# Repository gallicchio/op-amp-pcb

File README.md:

# Discrete Transistor Op-Amp

The op-amp of *Learning the Art of Electronics* (Hayes and Horowitz, 2016), Lab 5L,
built from six 2N3904 / 2N3906 transistors on a 100 x 100 mm board whose silkscreen
*is* the schematic.  For a first electronics lab: every node has a loop to hang a
scope probe on, three DIP switches select the variants the book walks through, and
the inputs, output and power come in on BNCs and screw terminals.

> "I want you to build a relatively inexpensive educational Op-Amp PCB out of discrete
> transistors that I'll order from JLCPCB using only components that they have
> available and in stock ... The silkscreen should look exactly like the schematic ...
> The primary goal is clarity, simplicity, educational value, and ease of use for
> students in their first electronics lab class after having done most of chapter 4
> in Learning the Art of Electronics."

**Only prompts.** The whole project came from [a conversation with Claude](CLAUDE_CODE_CHAT.md):
the schematic, the board, the simulation, the fab files and these documents are all
written by the Python under `scripts/` and `sim/`, and nothing was drawn by hand.

## What it is

The book's three-stage op-amp, with the book's values:

* **Difference amplifier**, Q1 and Q2, 1.5 k collector load, gain about 11.
* **Tail**: Q6 as a current sink (62 k / 10 k / 1 k), or the plain 10 k resistor the
  book starts with, on switch **TAIL**.
* **Gain stage**: Q3, a PNP common-emitter stage, 330 ohm / 12 k, gain about 30, with
  the 100 pF Miller compensation capacitor on switch **COMPENSATION**.
* **Push-pull emitter follower**, Q4 and Q5, into the book's 10 k / 1 k divider whose
  tap **X** is the feedback point for a gain of 11.
* Switch **FEEDBACK** closes the loop as the x11 amplifier (X to IN-) or as a follower
  (OUT to IN-), or leaves it open so you wire your own feedback through the
  screw terminals.

What the board adds, so a class of first-year students can use it:

* An **OFFSET NULL** trimmer between the two emitters (50 ohm, wiper to the tail).
* A **1 k in series with the 100 pF**, which cancels the Miller zero and makes the
  follower stable; COMPENSATION 2 shorts it so the book's bare 100 pF can be heard ringing.
* **Input protection**: 1 k in series with each input and anti-parallel 1N4148s between
  the bases, so no base-emitter junction ever sees its 6 V reverse breakdown.
* **Output protection** in one part: R17, 330 ohm from the push-pull to OUT, inside
  the loop, so a shorted output draws about 46 mA and Q4 and Q5 stay cool.  It also
  keeps a cable on OUT from making the follower ring.
* **Reverse-supply protection** (a Schottky in each rail) and a green LED per rail.
* 18 probe loops, four of them ground (one per scope channel), placed on every node
  the book asks you to look at.  Dashed boxes name each stage on the silkscreen, and
  every transistor sits inside its own symbol with B, C and E marked.

Parts cost about $7.79 in parts per board at JLCPCB; the fixed assembly fees make the
first board about $70 and each further one about $9, so about $15 each for 10 assembled boards.  See
[docs/MANUFACTURING.md](docs/MANUFACTURING.md).

## Using it

[docs/HANDBOOK.md](docs/HANDBOOK.md) is the student and instructor guide: how to
power it, what every switch and loop does, the quiescent voltage at every loop, the
bring-up order for a new board, and a set of exercises that follow Lab 5L stage by
stage.  The back of the board carries the short version.

## Building the files

Needs KiCad 10 (an AppImage is enough), Python 3 with `Pillow`, `pdftoppm`
(poppler-utils) for the images and, optionally, `libngspice` for the simulation.

```bash
git clone https://github.com/gallicchio/op-amp-pcb.git
cd op-amp-pcb
export KICAD_APPIMAGE=$HOME/.local/bin/kicad-10.0.7-x86_64.AppImage   # or kicad-cli on PATH
./make.py              # footprints, models, simulation, schematic, board, checks, fab files, docs
./make.py --clean      # delete everything it generates
```

The build stops on any ERC or DRC violation, on any of the 110 circuit assertions
that read the exported netlist back against the book's circuit, on a schematic text
overlap, on a fab-package problem (an order code whose JLCPCB description no longer
matches, a QR code that does not decode from the board file) and on any number in
these documents that no longer matches the build.

## Layout

```
make.py                one command builds and checks everything
scripts/parts.py       every part: value, footprint, LCSC code, stock, JLCPCB rotation
scripts/layout.py      the board: placements, the silkscreen wires, texts and boxes
scripts/gen_sch.py     writes hardware/opamp.kicad_sch
scripts/gen_pcb.py     writes hardware/opamp.kicad_pcb (copper follows the silk wires)
scripts/check_*.py     the netlist, the schematic sheet and the fab package
sim/opamp_sim.py       ngspice: operating point, loop gain, step response, swing, null
out/opamp/             gerbers, BOM, CPL (native and JLCPCB), prints, PLACEMENT_CHECKS
docs/                  MANUFACTURING, HANDBOOK, DESIGN_NOTES, images
```

## More

* [docs/DESIGN_NOTES.md](docs/DESIGN_NOTES.md): every departure from the book and why,
  the simulation numbers, the risks for a first board and the rev B list.
* [CLAUDE_CODE_CHAT.md](CLAUDE_CODE_CHAT.md): the conversation that produced it.

Circuit: Hayes and Horowitz.  Board: Jason Gallicchio and Claude.  Hardware under
CERN-OHL-P-2.0, scripts under MIT; see [LICENSE](LICENSE).

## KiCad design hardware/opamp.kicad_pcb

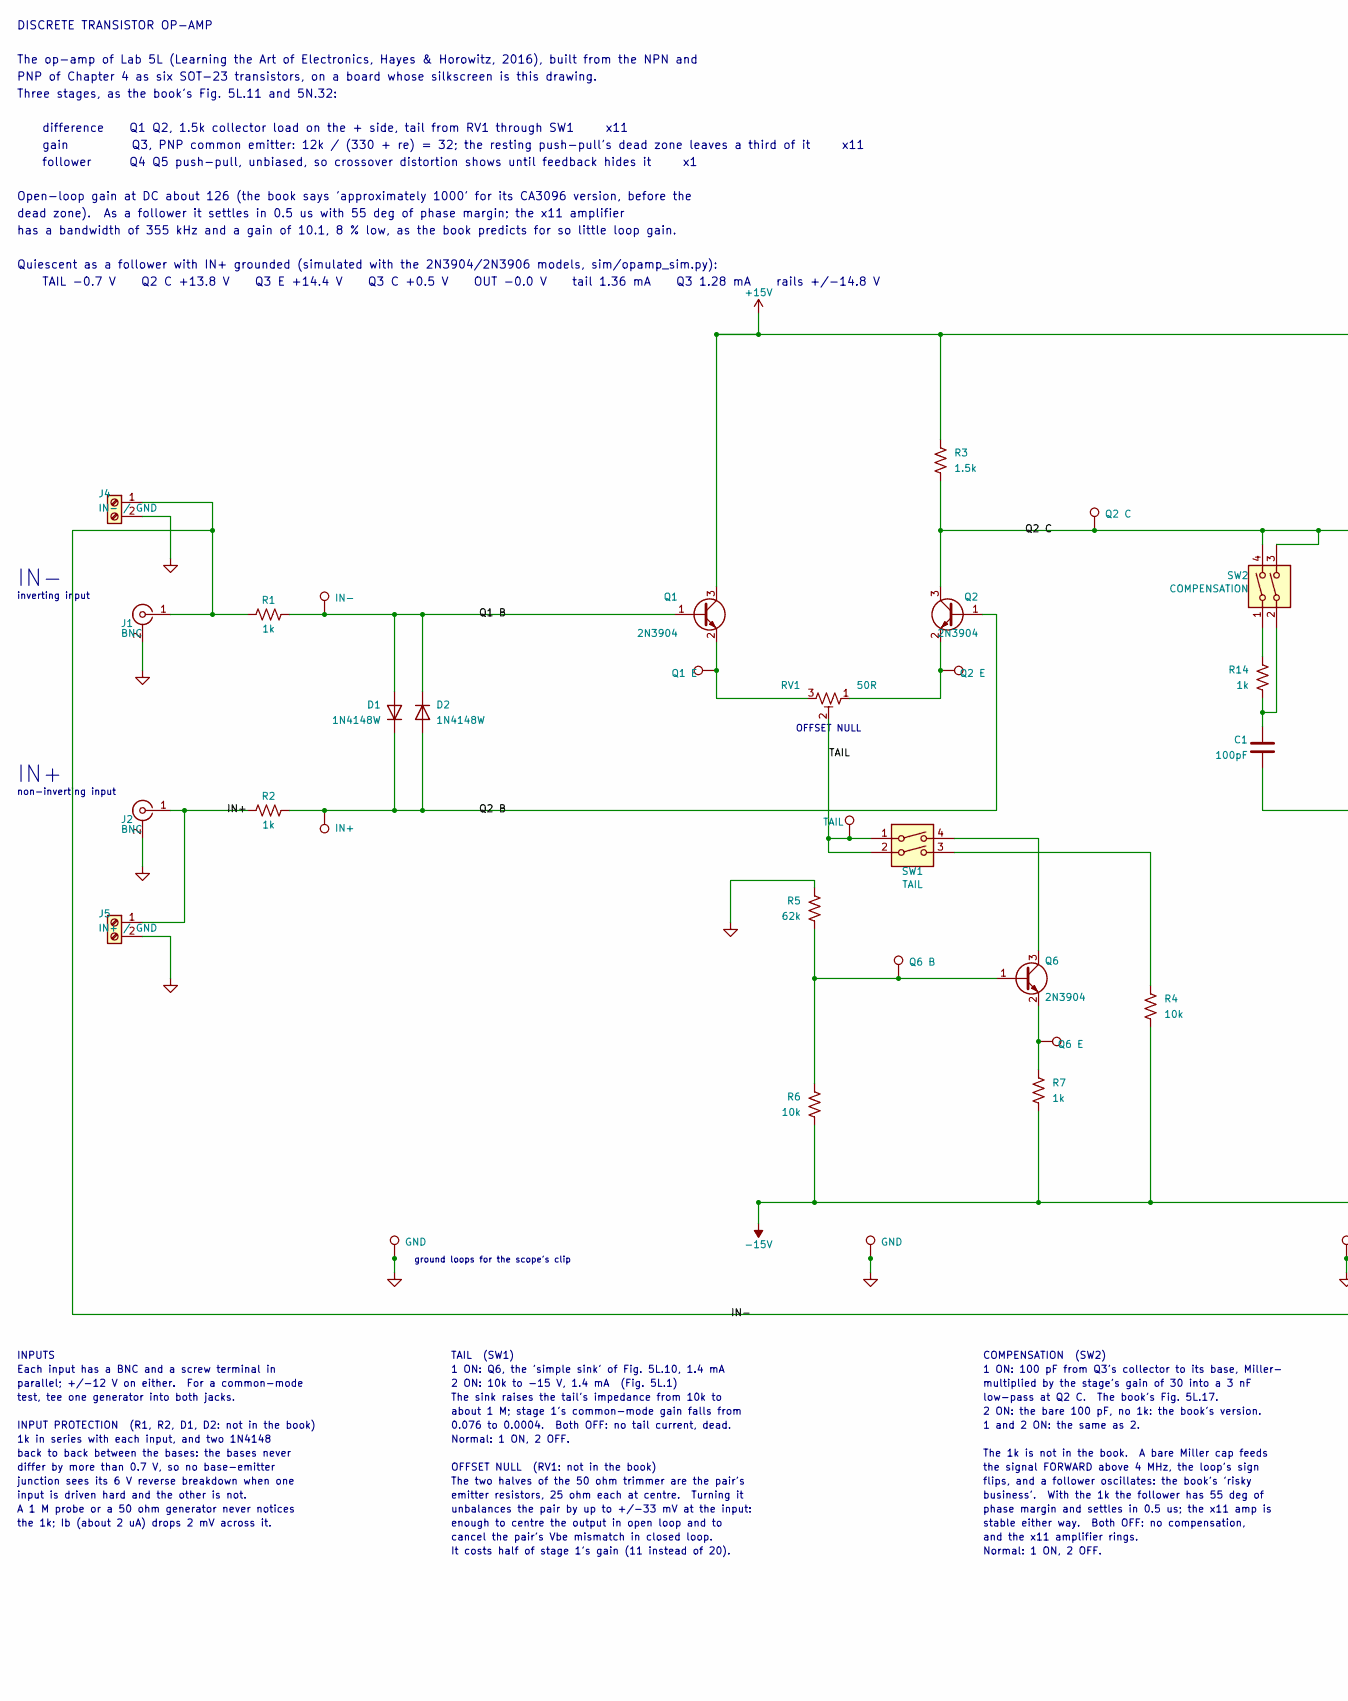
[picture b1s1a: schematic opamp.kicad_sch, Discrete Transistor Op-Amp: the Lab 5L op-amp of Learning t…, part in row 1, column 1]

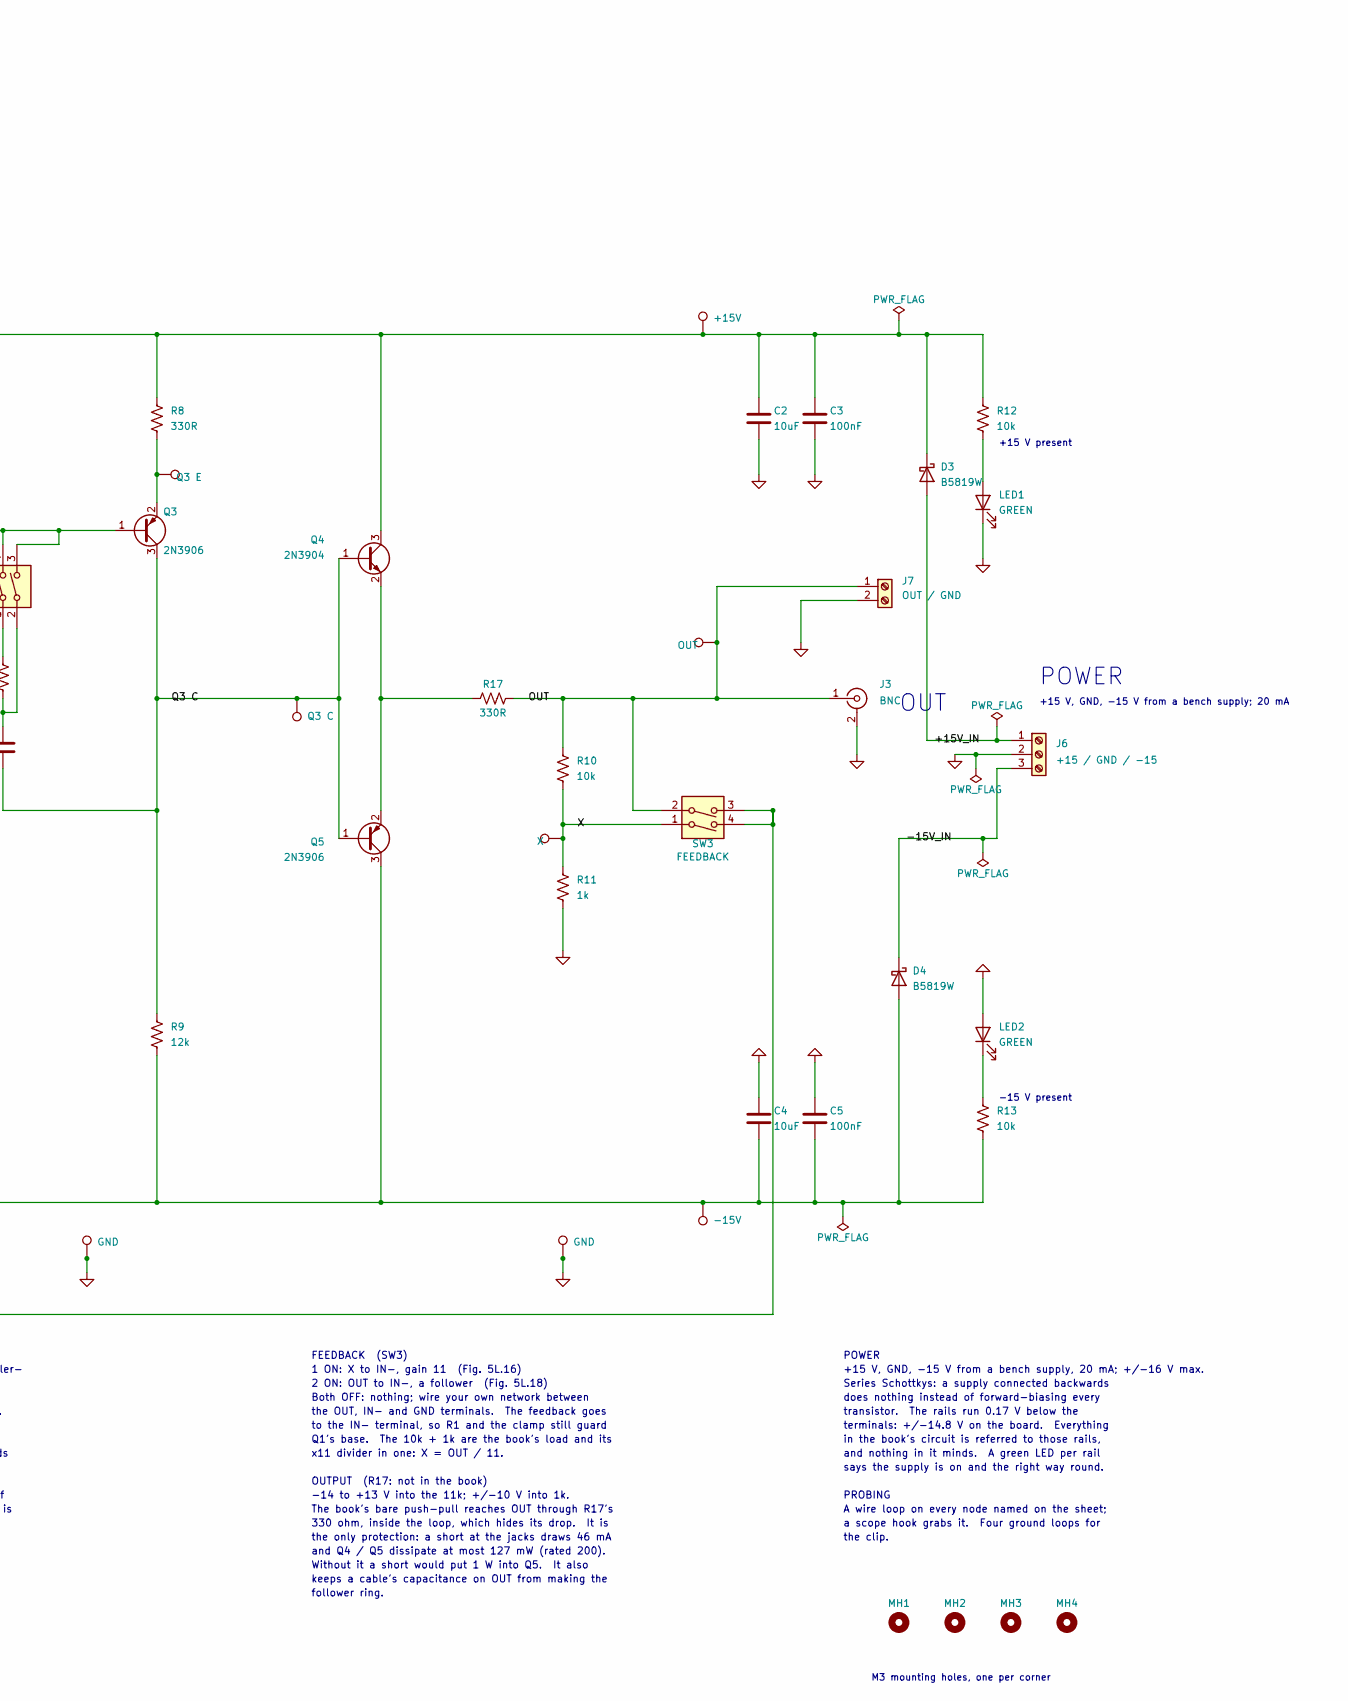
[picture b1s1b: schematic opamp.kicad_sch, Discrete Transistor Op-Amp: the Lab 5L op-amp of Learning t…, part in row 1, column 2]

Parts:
C1: 100pF; C_0805_2012Metric; MPN CL21C101JBANNNC; LCSC C1790
C2, C4: 10uF; C_0805_2012Metric; MPN CL21A106KAYNNNE; LCSC C15850
C3, C5: 100nF; C_0805_2012Metric; MPN CC0805KRX7R9BB104; LCSC C49678
D1, D2: 1N4148W; D_SOD-123; MPN 1N4148W; LCSC C81598
D3, D4: B5819W; D_SOD-123; MPN B5819W SL; LCSC C8598
J1, J2, J3: BNC; BNC_KYWE_RightAngle; MPN BNC-KYWE-295-W4-N; LCSC C41416668
J4: IN- / GND; TerminalBlock_KF301_1x02_P5.00mm; MPN KF301-5.0-2P; LCSC C474881
J5: IN+ / GND; TerminalBlock_KF301_1x02_P5.00mm; MPN KF301-5.0-2P; LCSC C474881
J6: +15 / GND / -15; TerminalBlock_KF301_1x03_P5.00mm; MPN KF301-5.0-3P; LCSC C474882
J7: OUT / GND; TerminalBlock_KF301_1x02_P5.00mm; MPN KF301-5.0-2P; LCSC C474881
LED1, LED2: GREEN; LED_0805_2012Metric; MPN KT-0805G; LCSC C2297
MH1, MH2, MH3, MH4: MountingHole; MountingHole_3.2mm_M3
Q1, Q2, Q4, Q6: 2N3904; SOT-23; MPN MMBT3904; LCSC C20526
Q3, Q5: 2N3906; SOT-23; MPN MMBT3906LT1G; LCSC C53444
R1, R2, R7: 1k; R_1206_3216Metric; MPN 1206W4F1001T5E; LCSC C4410
R3: 1.5k; R_0805_2012Metric; MPN 0805W8F1501T5E; LCSC C4310
R4, R6, R10, R12, R13: 10k; R_0805_2012Metric; MPN 0805W8F1002T5E; LCSC C17414
R5: 62k; R_0805_2012Metric; MPN 0805W8F6202T5E; LCSC C17783
R8, R17: 330R; R_2512_6332Metric; MPN FRC2512F3300TS; LCSC C2934068
R9: 12k; R_0805_2012Metric; MPN 0805W8F1202T5E; LCSC C17444
R11, R14: 1k; R_0805_2012Metric; MPN 0805W8F1001T5E; LCSC C17513
RV1: 50R; Potentiometer_Bourns_3362P_Vertical; MPN 3362P-1-500; LCSC C52754333
SW1: TAIL; SW_DIP_SPSTx02_KingTek_DSIC02_P2.54mm; MPN DSIC02LSGET; LCSC C54949
SW2: COMPENSATION; SW_DIP_SPSTx02_KingTek_DSIC02_P2.54mm; MPN DSIC02LSGET; LCSC C54949
SW3: FEEDBACK; SW_DIP_SPSTx02_KingTek_DSIC02_P2.54mm; MPN DSIC02LSGET; LCSC C54949
TP1: IN-; TestPoint_Loop_RH-5019; MPN RH-5019; LCSC C5199800
TP2: IN+; TestPoint_Loop_RH-5019; MPN RH-5019; LCSC C5199800
TP3: TAIL; TestPoint_Loop_RH-5019; MPN RH-5019; LCSC C5199800
TP4: Q6 E; TestPoint_Loop_RH-5019; MPN RH-5019; LCSC C5199800
TP5: Q6 B; TestPoint_Loop_RH-5019; MPN RH-5019; LCSC C5199800
TP6: Q2 C; TestPoint_Loop_RH-5019; MPN RH-5019; LCSC C5199800
TP7: Q3 E; TestPoint_Loop_RH-5019; MPN RH-5019; LCSC C5199800
TP8: Q3 C; TestPoint_Loop_RH-5019; MPN RH-5019; LCSC C5199800
TP9: OUT; TestPoint_Loop_RH-5019; MPN RH-5019; LCSC C5199800
TP10: X; TestPoint_Loop_RH-5019; MPN RH-5019; LCSC C5199800
TP11: +15V; TestPoint_Loop_RH-5019; MPN RH-5019; LCSC C5199800
TP12: -15V; TestPoint_Loop_RH-5019; MPN RH-5019; LCSC C5199800
TP13: Q1 E; TestPoint_Loop_RH-5019; MPN RH-5019; LCSC C5199800
TP14: Q2 E; TestPoint_Loop_RH-5019; MPN RH-5019; LCSC C5199800
TP100, TP101, TP102, TP103: GND; TestPoint_Loop_RH-5019; MPN RH-5019; LCSC C5199800

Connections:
+15V: C2.1, C3.1, D3.1 (K), Q1.3 (C), Q4.3 (C), R3.1, R8.1, R12.1, TP11.1
-15V: C4.2, C5.2, D4.2 (A), Q5.3 (C), R4.2, R6.2, R7.2, R9.2, R13.2, TP12.1
/+15V_IN: D3.2 (A), J6.1
/-15V_IN: D4.1 (K), J6.3
/IN+: J2.1 (In), J5.1, R2.1
/IN-: J1.1 (In), J4.1, R1.1, SW3.3, SW3.4
/OUT: J3.1 (In), J7.1, R10.1, R17.2, SW3.2, TP9.1
/Q1 B: D1.2 (A), D2.1 (K), Q1.1 (B), R1.2, TP1.1
/Q2 B: D1.1 (K), D2.2 (A), Q2.1 (B), R2.2, TP2.1
/Q2 C: Q2.3 (C), Q3.1 (B), R3.2, SW2.3, SW2.4, TP6.1
/Q3 C: C1.2, Q3.3 (C), Q4.1 (B), Q5.1 (B), R9.1, TP8.1
/TAIL: RV1.2, SW1.1, SW1.2, TP3.1
/X: R10.2, R11.1, SW3.1, TP10.1
GND: C2.2, C3.2, C4.1, C5.1, J1.2 (Ext), J2.2 (Ext), J3.2 (Ext), J4.2, J5.2, J6.2, J7.2, LED1.1 (K), LED2.2 (A), R5.1, R11.2, TP100.1, TP101.1, TP102.1, TP103.1
unnamed: C1.1, R14.2, SW2.2
unnamed: LED1.2 (A), R12.2
unnamed: LED2.1 (K), R13.1
unnamed: Q1.2 (E), RV1.3, TP13.1
unnamed: Q2.2 (E), RV1.1, TP14.1
unnamed: Q3.2 (E), R8.2, TP7.1
unnamed: Q4.2 (E), Q5.2 (E), R17.1
unnamed: Q6.1 (B), R5.2, R6.1, TP5.1
unnamed: Q6.3 (C), SW1.4
unnamed: Q6.2 (E), R7.1, TP4.1
unnamed: R4.1, SW1.3
unnamed: R14.1, SW2.1

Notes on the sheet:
stable either way. Both OFF: no compensation,
dead zone). As a follower it settles in 0.5 us with 55 deg of phase margin; the x11 amplifier
POWER
0.076 to 0.0004. Both OFF: no tail current, dead.
difference Q1 Q2, 1.5k collector load on the + side, tail from RV1 through SW1 x11
PROBING
unbalances the pair by up to +/-33 mV at the input:
has a bandwidth of 355 kHz and a gain of 10.1, 8 % low, as the book predicts for so little loop gain.
+15 V, GND, -15 V from a bench supply; 20 mA
The 1k is not in the book. A bare Miller cap feeds
non-inverting input
It costs half of stage 1's gain (11 instead of 20).
business'. With the 1k the follower has 55 deg of
OUTPUT (R17: not in the book)
-14 to +13 V into the 11k; +/-10 V into 1k.
1 ON: Q6, the 'simple sink' of Fig. 5L.10, 1.4 mA
does nothing instead of forward-biasing every
The sink raises the tail's impedance from 10k to
the signal FORWARD above 4 MHz, the loop's sign
OFFSET NULL (RV1: not in the book)
Open-loop gain at DC about 126 (the book says 'approximately 1000' for its CA3096 version, before the
emitter resistors, 25 ohm each at centre. Turning it
The two halves of the 50 ohm trimmer are the pair's
back to back between the bases: the bases never
phase margin and settles in 0.5 us; the x11 amp is
-15 V present
and Q4 / Q5 dissipate at most 127 mW (rated 200).
Normal: 1 ON, 2 OFF.
cancel the pair's Vbe mismatch in closed loop.
follower ring.
INPUTS
TAIL (SW1)
+15 V, GND, -15 V from a bench supply, 20 mA; +/-16 V max.
INPUT PROTECTION (R1, R2, D1, D2: not in the book)
PNP of Chapter 4 as six SOT-23 transistors, on a board whose silkscreen is this drawing.
2 ON: 10k to -15 V, 1.4 mA (Fig. 5L.1)
OFFSET NULL
to the IN- terminal, so R1 and the clamp still guard
TAIL -0.7 V Q2 C +13.8 V Q3 E +14.4 V Q3 C +0.5 V OUT -0.0 V tail 1.36 mA Q3 1.28 mA rails +/-14.8 V
A wire loop on every node named on the sheet;

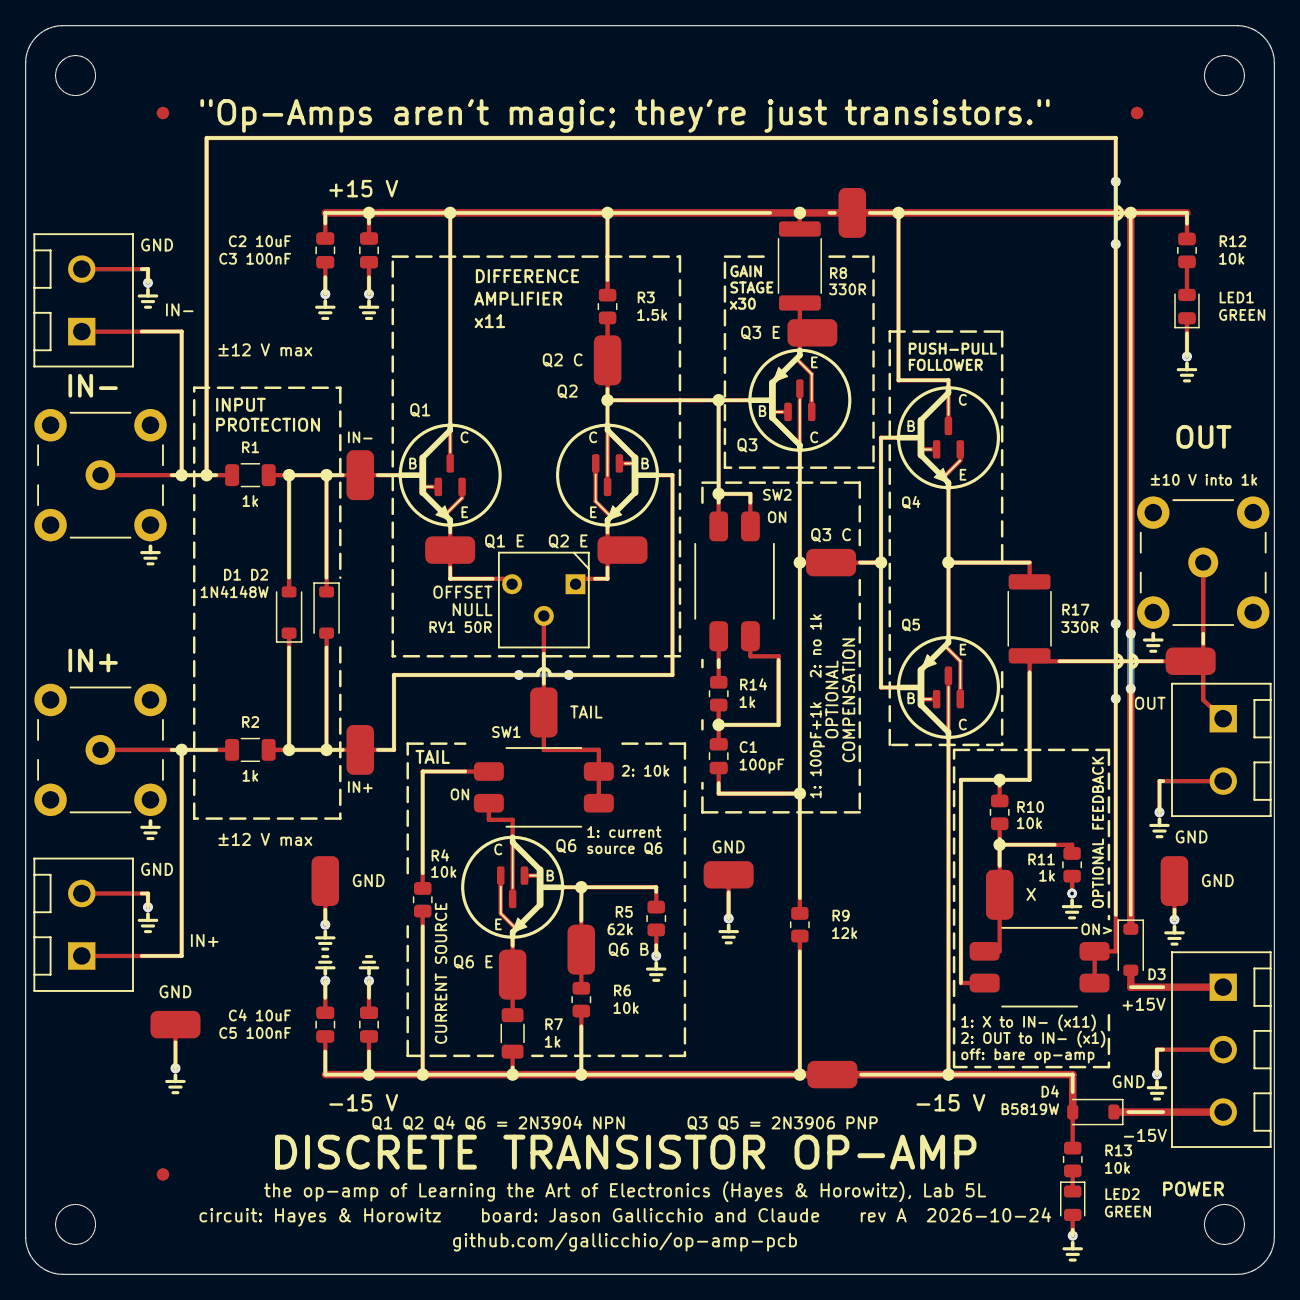
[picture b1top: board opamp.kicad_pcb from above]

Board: 2 copper layers, 100.0 x 100.0 mm, 65 parts (0 on the bottom side), 26 nets.

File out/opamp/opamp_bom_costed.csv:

Comment,Designator,Footprint,LCSC Part #,MPN,Qty,Unit $,Ext $,JLC
100pF,C1,C_0805_2012Metric,C1790,CL21C101JBANNNC,1,0.0101,0.010,basic
10uF,"C2,C4",C_0805_2012Metric,C15850,CL21A106KAYNNNE,2,0.0426,0.085,basic
100nF,"C3,C5",C_0805_2012Metric,C49678,CC0805KRX7R9BB104,2,0.0205,0.041,basic
1N4148W,"D1,D2",D_SOD-123,C81598,1N4148W,2,0.0124,0.025,basic
B5819W,"D3,D4",D_SOD-123,C8598,B5819W SL,2,0.0260,0.052,basic
IN- / GND,J4,TerminalBlock_KF301_1x02_P5.00mm,C474881,KF301-5.0-2P,1,0.1020,0.102,extended
IN+ / GND,J5,TerminalBlock_KF301_1x02_P5.00mm,C474881,KF301-5.0-2P,1,0.1020,0.102,extended
+15 / GND / -15,J6,TerminalBlock_KF301_1x03_P5.00mm,C474882,KF301-5.0-3P,1,0.1400,0.140,extended
OUT / GND,J7,TerminalBlock_KF301_1x02_P5.00mm,C474881,KF301-5.0-2P,1,0.1020,0.102,extended
BNC,"J1,J2,J3",BNC_KYWE_RightAngle,C41416668,BNC-KYWE-295-W4-N,3,1.2930,3.879,extended
GREEN,"LED1,LED2",LED_0805_2012Metric,C2297,KT-0805G,2,0.0164,0.033,basic
2N3906,"Q3,Q5",SOT-23,C53444,MMBT3906LT1G,2,0.0190,0.038,extended
2N3904,"Q1,Q2,Q4,Q6",SOT-23,C20526,MMBT3904,4,0.0116,0.046,basic
1.5k,R3,R_0805_2012Metric,C4310,0805W8F1501T5E,1,0.0028,0.003,basic
62k,R5,R_0805_2012Metric,C17783,0805W8F6202T5E,1,0.0021,0.002,preferred
12k,R9,R_0805_2012Metric,C17444,0805W8F1202T5E,1,0.0028,0.003,basic
50R,RV1,Potentiometer_Bourns_3362P_Vertical,C52754333,3362P-1-500,1,0.3370,0.337,extended
330R,"R8,R17",R_2512_6332Metric,C2934068,FRC2512F3300TS,2,0.0348,0.070,extended
1k,"R11,R14",R_0805_2012Metric,C17513,0805W8F1001T5E,2,0.0035,0.007,basic
1k,"R1,R2,R7",R_1206_3216Metric,C4410,1206W4F1001T5E,3,0.0085,0.026,basic
10k,"R4,R6,R10,R12,R13",R_0805_2012Metric,C17414,0805W8F1002T5E,5,0.0034,0.017,basic
TAIL,SW1,SW_DIP_SPSTx02_KingTek_DSIC02_P2.54mm,C54949,DSIC02LSGET,1,0.3080,0.308,extended
COMPENSATION,SW2,SW_DIP_SPSTx02_KingTek_DSIC02_P2.54mm,C54949,DSIC02LSGET,1,0.3080,0.308,extended
FEEDBACK,SW3,SW_DIP_SPSTx02_KingTek_DSIC02_P2.54mm,C54949,DSIC02LSGET,1,0.3080,0.308,extended
IN-,TP1,TestPoint_Loop_RH-5019,C5199800,RH-5019,1,0.0966,0.097,extended
IN+,TP2,TestPoint_Loop_RH-5019,C5199800,RH-5019,1,0.0966,0.097,extended
TAIL,TP3,TestPoint_Loop_RH-5019,C5199800,RH-5019,1,0.0966,0.097,extended
Q6 E,TP4,TestPoint_Loop_RH-5019,C5199800,RH-5019,1,0.0966,0.097,extended
Q6 B,TP5,TestPoint_Loop_RH-5019,C5199800,RH-5019,1,0.0966,0.097,extended
Q2 C,TP6,TestPoint_Loop_RH-5019,C5199800,RH-5019,1,0.0966,0.097,extended
Q3 E,TP7,TestPoint_Loop_RH-5019,C5199800,RH-5019,1,0.0966,0.097,extended
Q3 C,TP8,TestPoint_Loop_RH-5019,C5199800,RH-5019,1,0.0966,0.097,extended
OUT,TP9,TestPoint_Loop_RH-5019,C5199800,RH-5019,1,0.0966,0.097,extended
X,TP10,TestPoint_Loop_RH-5019,C5199800,RH-5019,1,0.0966,0.097,extended
+15V,TP11,TestPoint_Loop_RH-5019,C5199800,RH-5019,1,0.0966,0.097,extended
-15V,TP12,TestPoint_Loop_RH-5019,C5199800,RH-5019,1,0.0966,0.097,extended
Q1 E,TP13,TestPoint_Loop_RH-5019,C5199800,RH-5019,1,0.0966,0.097,extended
Q2 E,TP14,TestPoint_Loop_RH-5019,C5199800,RH-5019,1,0.0966,0.097,extended
GND,"TP100,TP101,TP102,TP103",TestPoint_Loop_RH-5019,C5199800,RH-5019,4,0.0966,0.386,extended

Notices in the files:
hardware/opamp.kicad_sch:
Open source, CERN-OHL-P-2.0 -- github.com/gallicchio/op-amp-pcb
